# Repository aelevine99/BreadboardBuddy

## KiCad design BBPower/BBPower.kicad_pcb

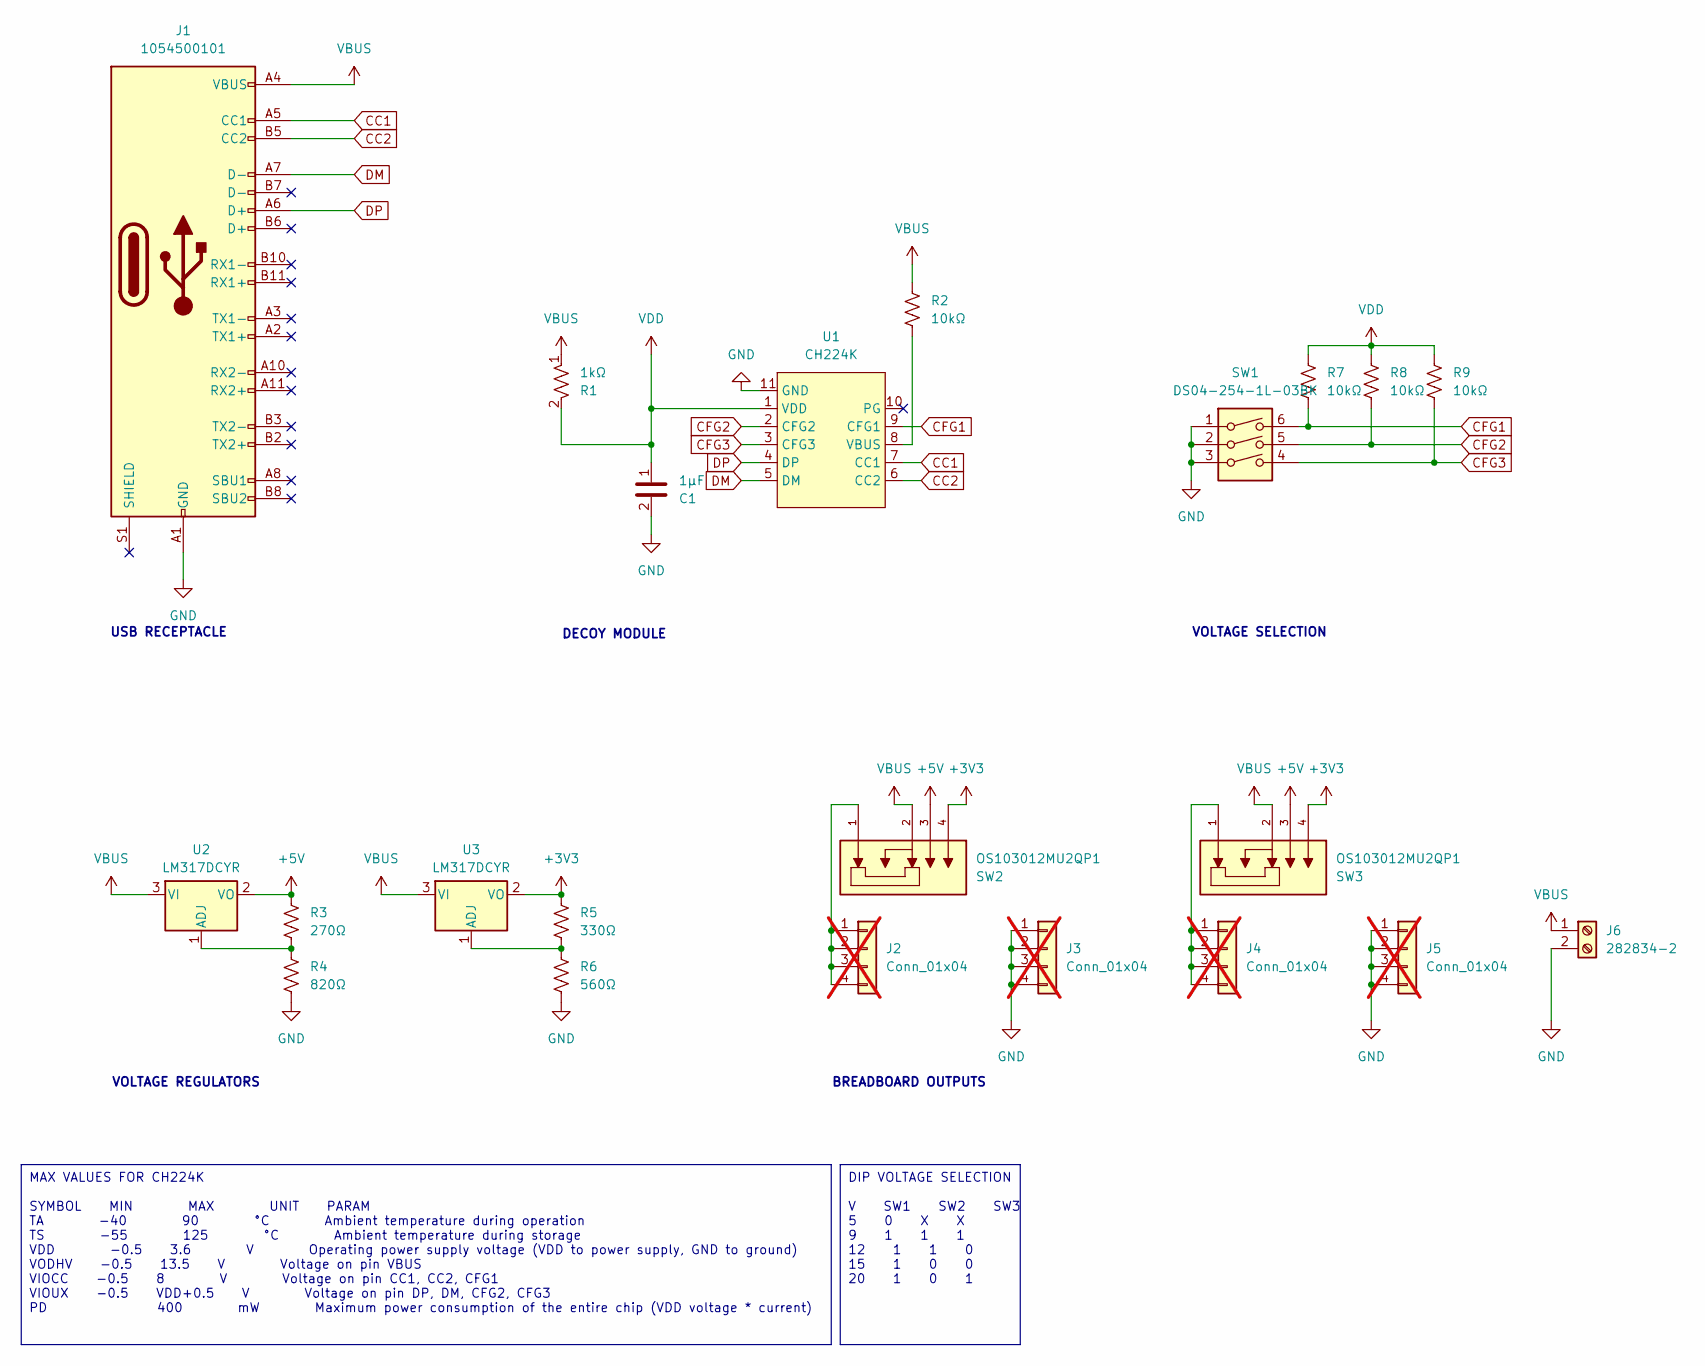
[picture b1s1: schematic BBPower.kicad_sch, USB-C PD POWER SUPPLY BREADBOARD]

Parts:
C1: 1μF; C_1206_3216Metric_Pad1.33x1.80mm_HandSolder
J1: 1054500101; USB_C_Receptacle_Molex_105450-0101
J2, J3, J4, J5: Conn_01x04; PinHeader_1x04_P2.54mm_Vertical; not fitted
J6: 282834-2; TerminalBlock_TE_282834-2_1x02_P2.54mm_Horizontal
R1: 1kΩ; R_1206_3216Metric_Pad1.30x1.75mm_HandSolder
R2, R7, R8, R9: 10kΩ; R_1206_3216Metric_Pad1.30x1.75mm_HandSolder
R3: 270Ω; R_1206_3216Metric_Pad1.30x1.75mm_HandSolder
R4: 820Ω; R_1206_3216Metric_Pad1.30x1.75mm_HandSolder
R5: 330Ω; R_1206_3216Metric_Pad1.30x1.75mm_HandSolder
R6: 560Ω; R_1206_3216Metric_Pad1.30x1.75mm_HandSolder
SW1: DS04-254-1L-03BK; SW_DS04-254-1L-03BK
SW2, SW3: OS103012MU2QP1; SW_OS103012MU2QP1; PARTREV 8 AUG 17
U1: CH224K; SSOP-10-1EP_3.9x4.9mm_P1mm_EP2.1x3.3mm
U2, U3: LM317DCYR; SOT-223-3_TabPin2

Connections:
+3V3: R5.1, SW2.4, SW3.4, U3.2 (VO)
+5V: R3.1, SW2.3, SW3.3, U2.2 (VO)
CC1: J1.A5 (CC1), U1.7 (CC1)
CC2: J1.B5 (CC2), U1.6 (CC2)
CFG1: R7.1, SW1.6, U1.9 (CFG1)
CFG2: R8.1, SW1.5, U1.2 (CFG2)
CFG3: R9.1, SW1.4, U1.3 (CFG3)
DM: J1.A7 (D-), U1.5 (DM)
DP: J1.A6 (D+), U1.4 (DP)
GND: C1.2, J1.A1 (GND), J1.A12 (GND), J1.B1 (GND), J1.B12 (GND), J3.1, J3.2, J3.3, J3.4, J5.1, J5.2, J5.3, J5.4, J6.2, R4.2, R6.2, SW1.1, SW1.2, SW1.3, U1.11 (GND)
unnamed: J2.1, J2.2, J2.3, J2.4, SW2.1
unnamed: J4.1, J4.2, J4.3, J4.4, SW3.1
unnamed: R2.1, U1.8 (VBUS)
unnamed: R3.2, R4.1, U2.1 (ADJ)
unnamed: R5.2, R6.1, U3.1 (ADJ)
VBUS: J1.A4 (VBUS), J1.A9 (VBUS), J1.B4 (VBUS), J1.B9 (VBUS), J6.1, R1.1, R2.2, SW2.2, SW3.2, U2.3 (VI), U3.3 (VI)
VDD: C1.1, R1.2, R7.2, R8.2, R9.2, U1.1 (VDD)

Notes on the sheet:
MAX VALUES FOR CH224K SYMBOL MIN MAX UNIT PARAM TA -40 90 °C Ambient temperature during operation TS -55 125 °C Ambient temperature during storage VDD -0.5 3.6 V Operating power supply voltage (VDD to power supply, GND to ground) VODHV -0.5 13.5 V Voltage on pin VBUS VIOCC -0.5 8 V Voltage on pin C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
DIP VOLTAGE SELECTION V SW1 SW2 SW3 5 0 X X 9 1 1 1 12 1 1 0 15 1 0 0 20 1 0 1
VOLTAGE SELECTION
USB RECEPTACLE
DECOY MODULE
BREADBOARD OUTPUTS
VOLTAGE REGULATORS

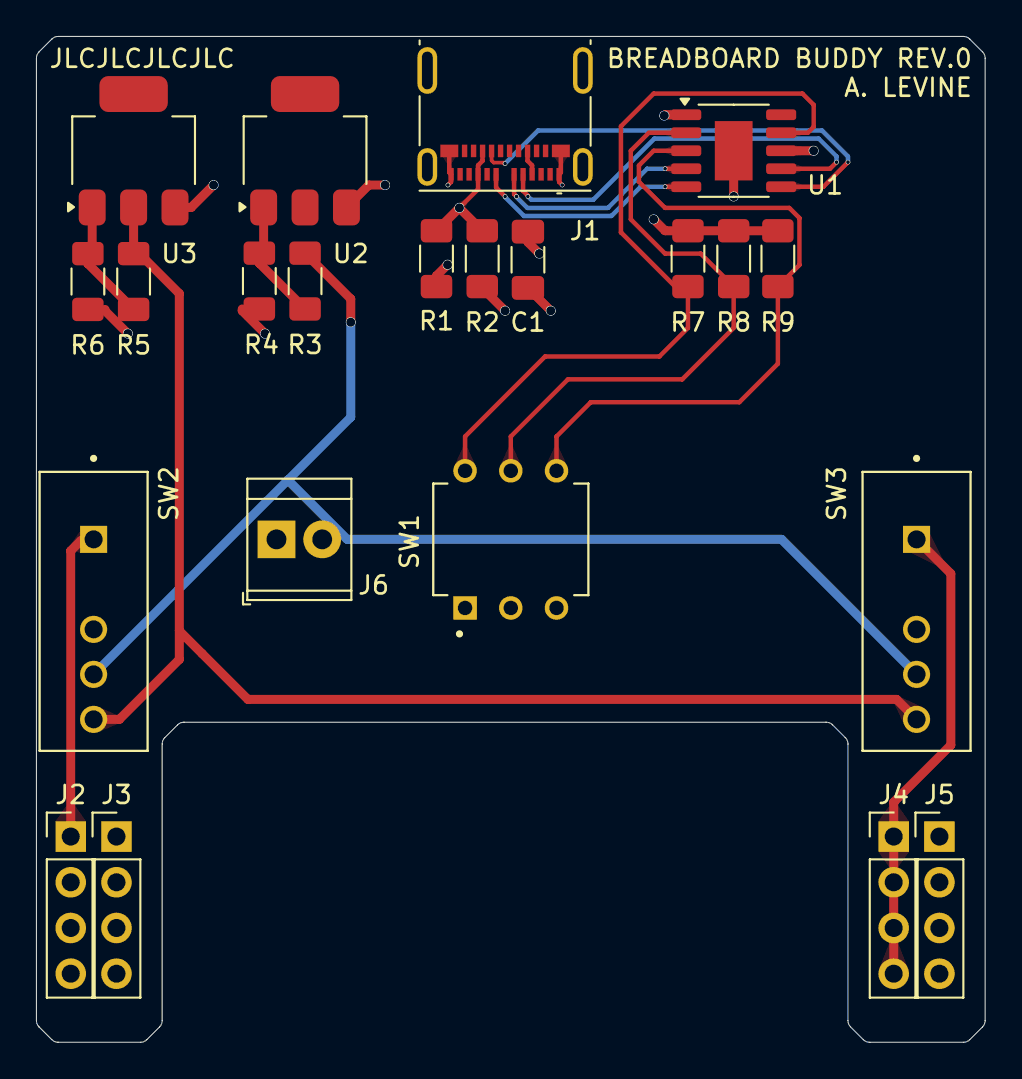
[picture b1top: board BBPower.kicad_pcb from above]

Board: 4 copper layers, 52.7 x 55.9 mm, 22 parts (0 on the bottom side), 17 nets.

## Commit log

2025-02-04 initial chip selection
2025-02-04 changed chip to decoy module
2025-02-04 schematic layout
2025-02-04 started pcb layout
2025-02-05 psb layout
2025-02-06 pcb updates & production file
2025-02-06 fixed bom & updated prod files
